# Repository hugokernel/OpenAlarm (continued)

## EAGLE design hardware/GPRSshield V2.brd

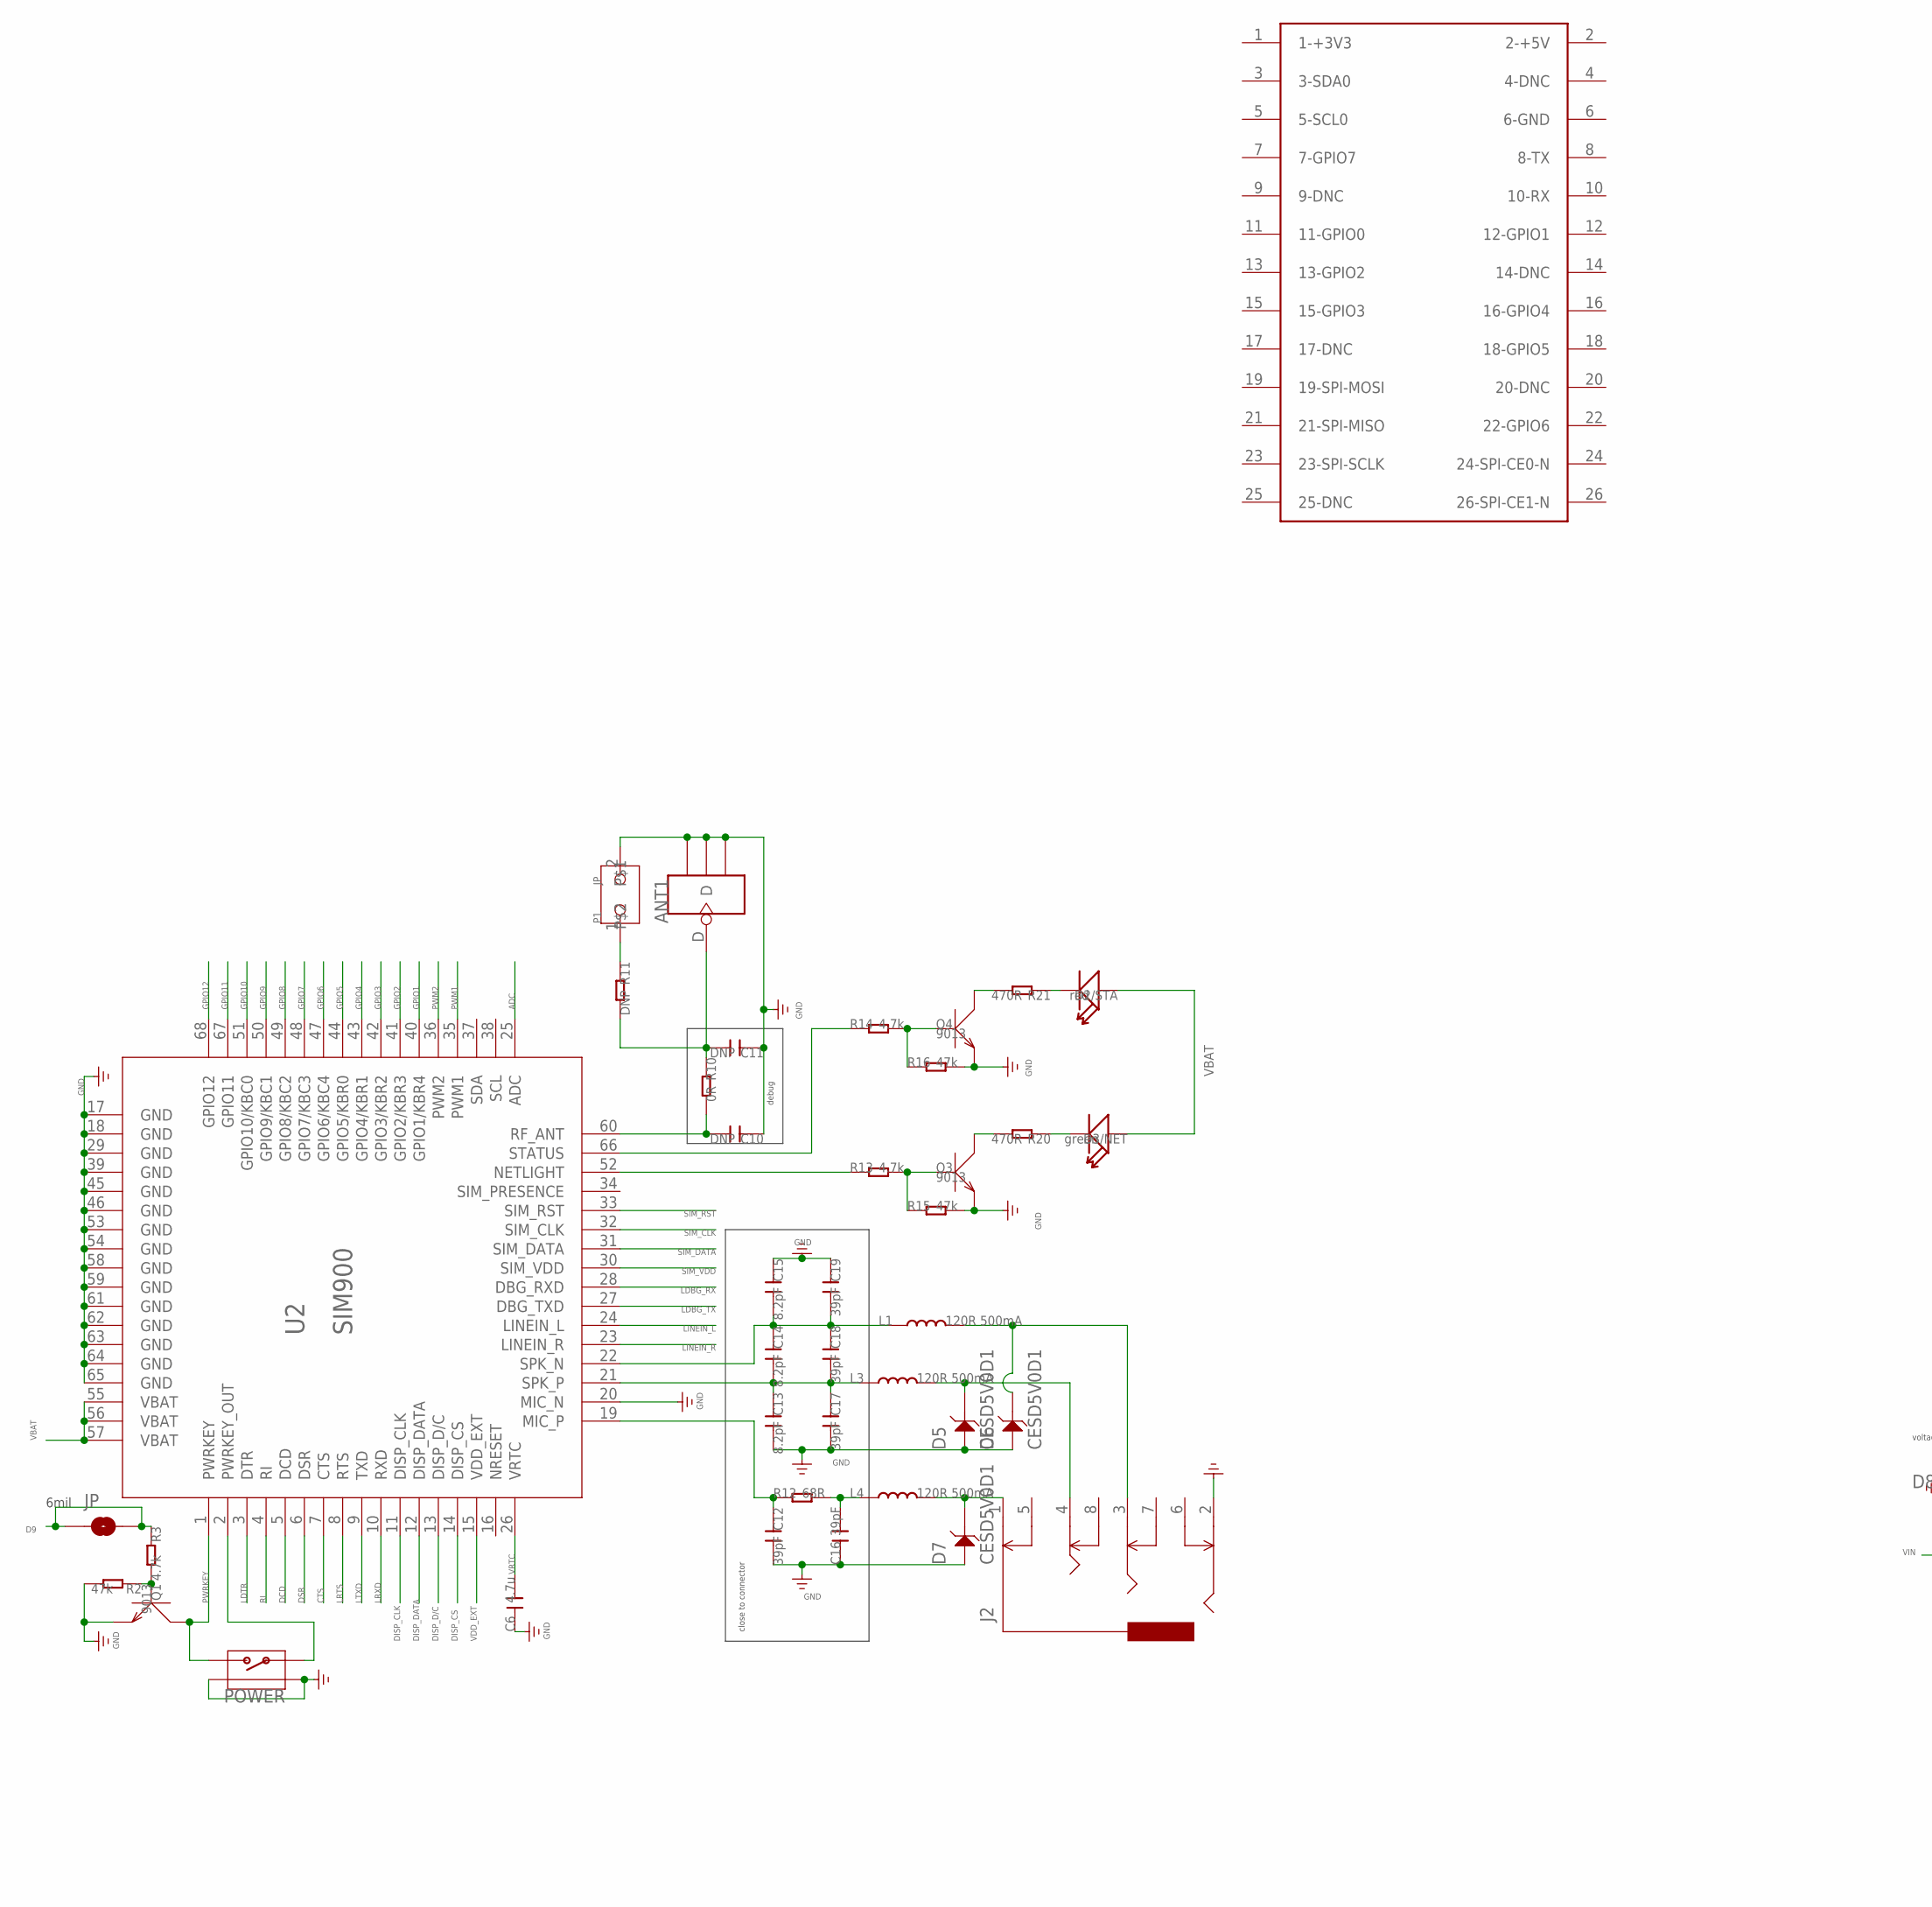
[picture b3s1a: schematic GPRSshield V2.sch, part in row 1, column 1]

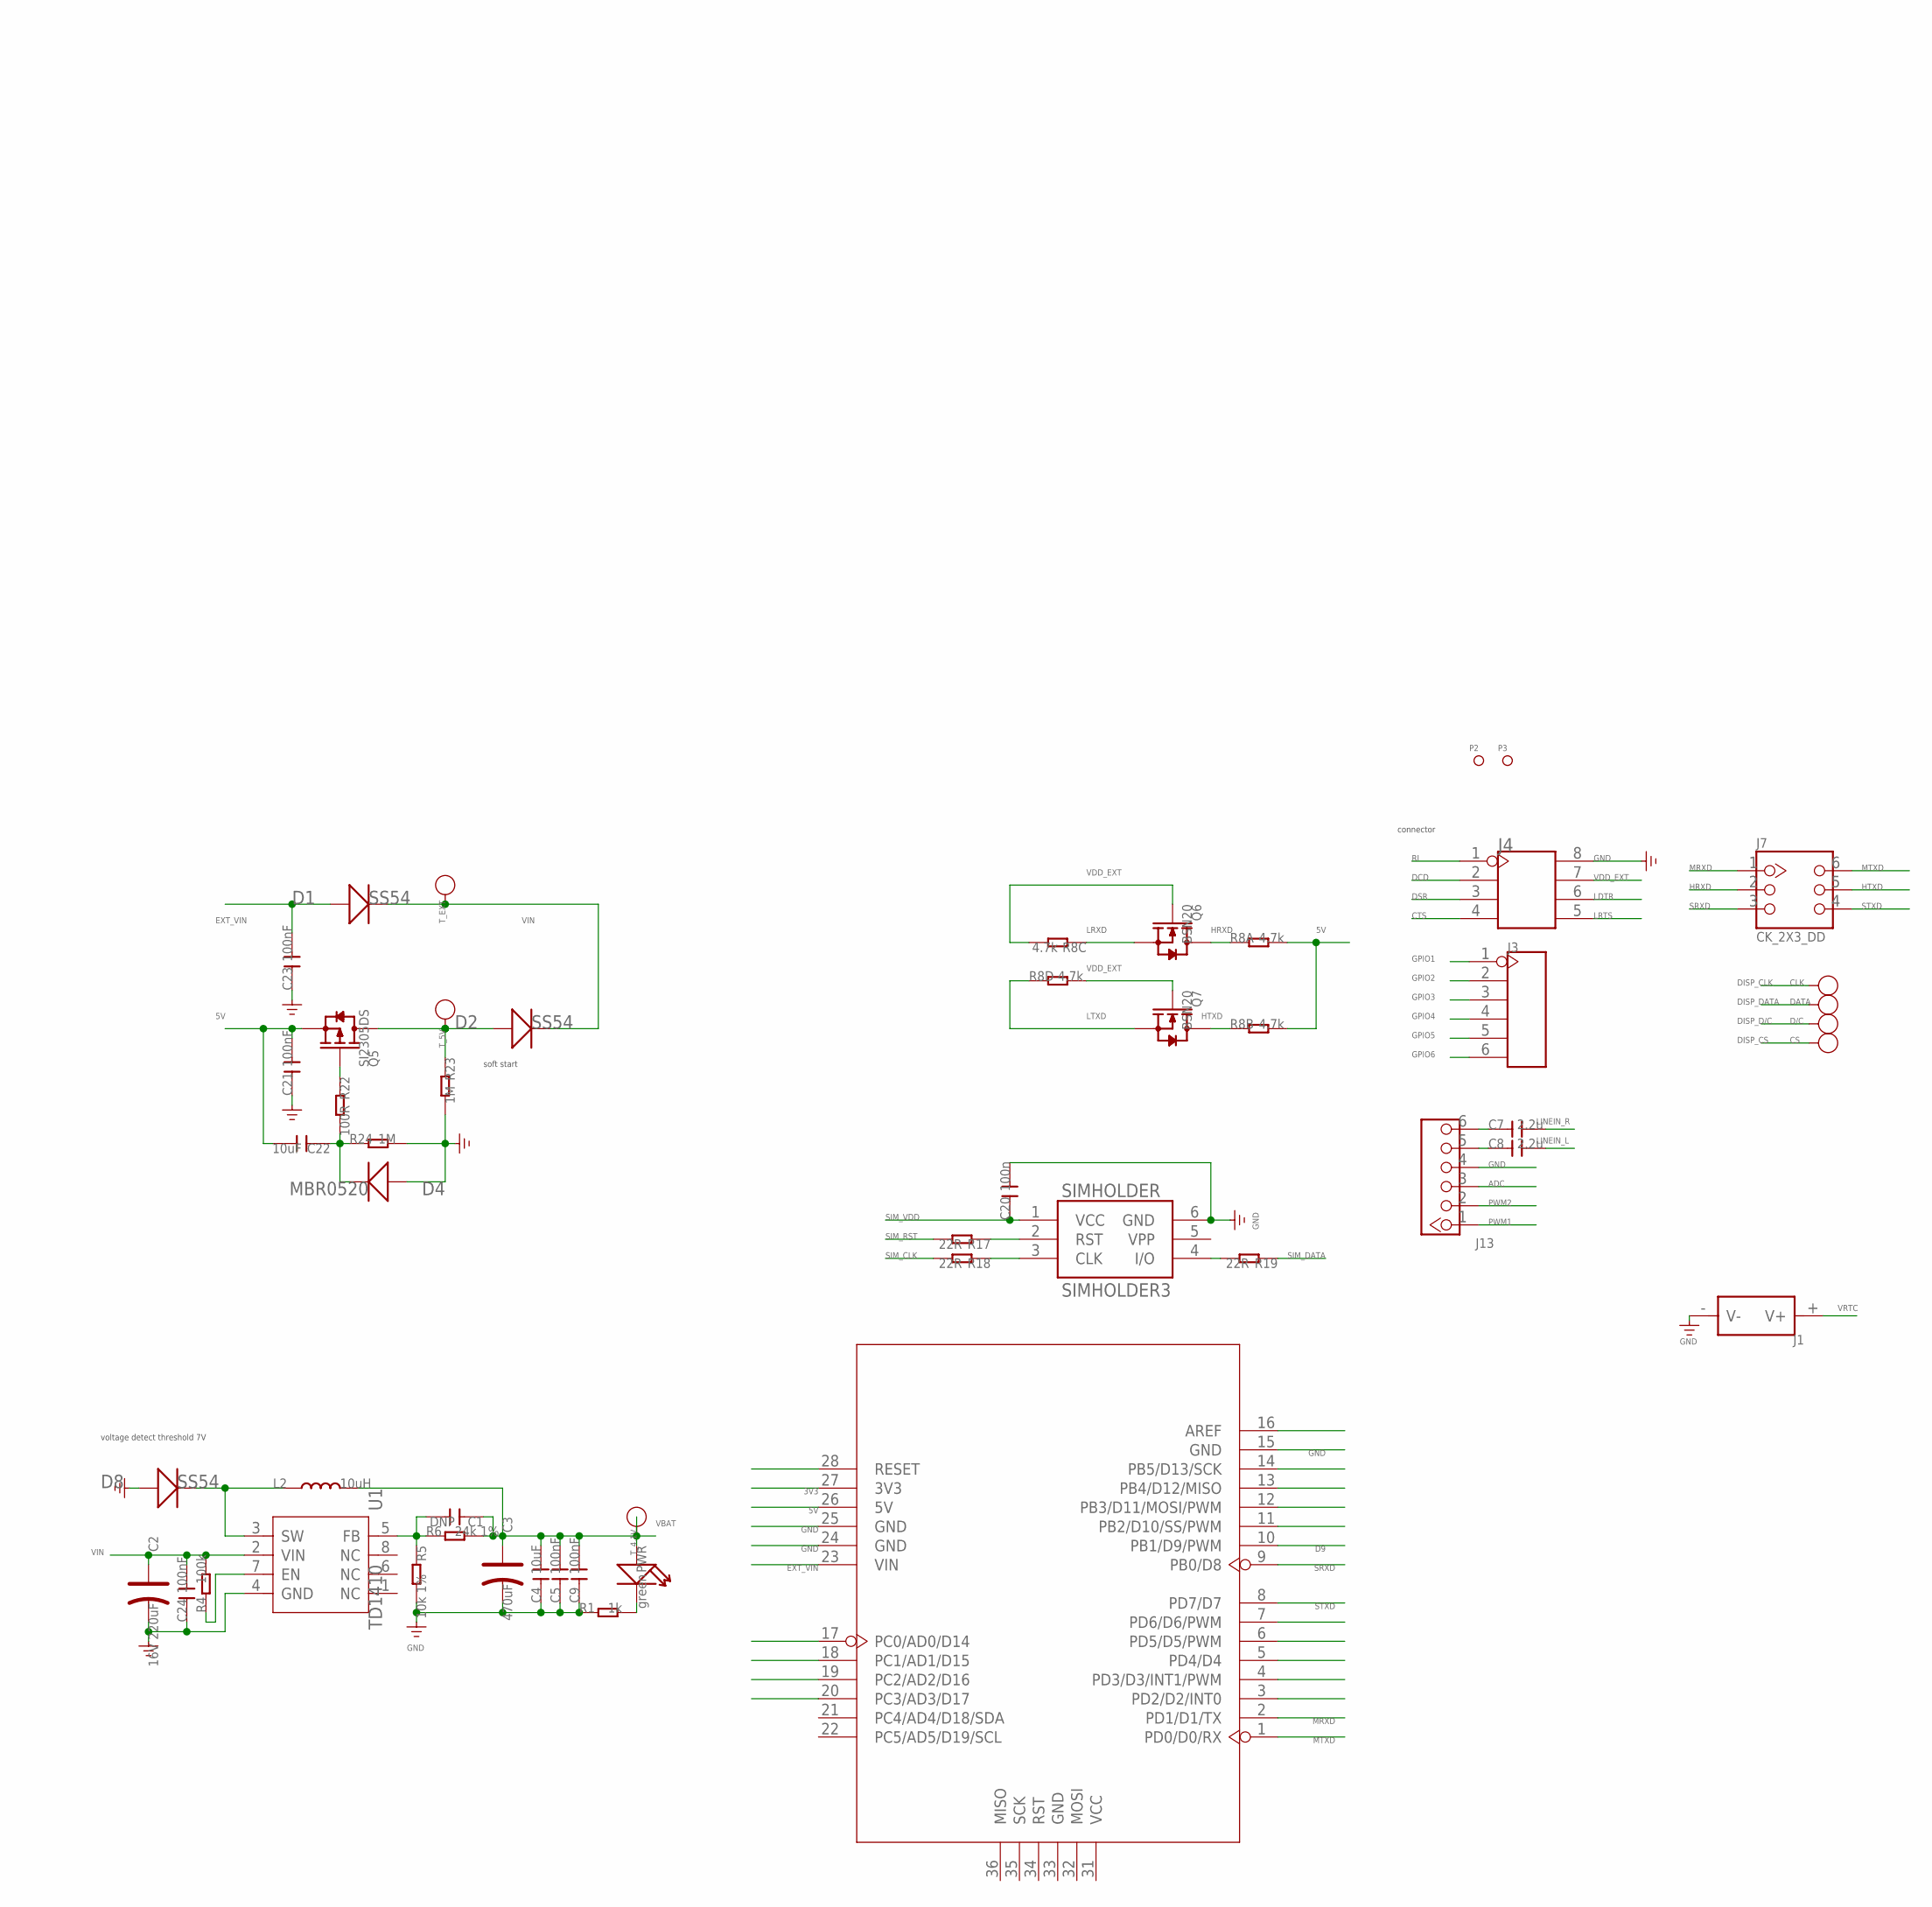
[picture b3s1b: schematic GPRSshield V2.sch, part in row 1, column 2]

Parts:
ANT1: ANTENNA-U-FL; 4P-U-FL
C1, C10, C11: DNP; C0603
C2: 16V 220uF; ELECTRO-SMD-D-5.6MM
C3: 470uF; AVX-D
C4, C22: 10uF; C0805
C5, C9, C21, C23, C24: 100nF; C0603
C6: 4.7u; C0805
C7, C8: 2.2u; C0805
C12, C16, C17, C18, C19: 39pF; C0603
C13, C14, C15: 8.2pF; C0603
C20: 100n; C0603
CLK: PAD-TEST-POINT-CIRCLE'4545'; TP_4545
CS: PAD-TEST-POINT-CIRCLE'4545'; TP_4545
D1, D2, D8: SS54; SMB
D2/STA: red; LED-0603
D3/NET: green; LED-0603
D4: MBR0520; SOD123-2.7X1.6
D5, D6, D7: CESD5V0D1; SOD123-2.7X1.6
D/C: PAD-TEST-POINT-CIRCLE'4545'; TP_4545
DATA: PAD-TEST-POINT-CIRCLE'4545'; TP_4545
J1: HOLDER-BAT; SMD-CR1220-2
J2: AUDIO-8P'PJ-3536-L6S'; 8P-3.5-SMD
J3: HEADER-6P-65/35MIL; 6P-2.54-65/35MIL
J4: HEADER-2X4P-2.54; 2X4P-2.54
J7: CK_2X3_DD; CK_2X3
J13: HEADER_1X6; CK_1X6
JP: PAD-SOLDERJUMPERNC; 2P-SMD-3.3X2
L1, L3, L4: 120R 500mA; L0603
L2: 10uH; L0630
P1: JP
P2, P3: PAD-MARK; ROUND-MARK-1.0
POWER: BUTTON-4P-REINFORCE'TS-118E'; 4P-SMD-7X3.5X3.5H
PWR: green; D0603
Q1, Q3, Q4: 9013; SOT23
Q5: SI2305DS; SOT23
Q6, Q7: BSN20; SOT23
R1: 1k; R0603
R2, R15, R16: 47k; R0603
R3, R13, R14: 4.7k; R0603
R4: 100k; R0603
R5: 10k 1%; R0603
R6: 24k 1%; R0603
R8: 4.7k; 1206-8-3.3X2.4
R10: 0R; R0603
R11: DNP; R0603
R12: 68R; R0603
R17, R18, R19: 22R; R0603
R20, R21: 470R; R0603
R22: 100R; R0603
R23, R24: 1M; R0603
SIMHOLDER: SIMHOLDER3
T_4.1V, T_5V: PAD-TEST-POINT-CIRCLE'4545'; TP_4545; PARTNO DNP
T_EXT: PAD-TEST-POINT-CIRCLE'4545'; TP_4545; PARTNO DNP
U1: TD1410; SOP8
U2: SIM900
U3: ARDUINO'W/O-SILK'; ARDUINO-W/O-SILK
U$4: RASPBERRY-PI

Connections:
3V3: U3.27 (3V3)
5V: C21.2, C22.2, Q5.2 (S), R8.7 (2), R8.8 (2), U3.26 (5V)
ADC: J13.3, U2.25 (ADC)
CTS: J4.4, U2.7 (CTS)
D9: JP.1, JP.2, R3.1, U3.10 (PB1/D9/PWM)
DCD: J4.2, U2.5 (DCD)
DISP_CLK: CLK.T, U2.11 (DISP_CLK)
DISP_CS: CS.T, U2.14 (DISP_CS)
DISP_D/C: D/C.T, U2.13 (DISP_D/C)
DISP_DATA: DATA.T, U2.12 (DISP_DATA)
DSR: J4.3, U2.6 (DSR)
EXT_VIN: C23.2, D1.+, U3.23 (VIN)
GND: ANT1.GND1, ANT1.GND2, ANT1.GND3, C2.-, C3.-, C4.1, C5.1, C6.1, C9.1, C10.1, C11.1, C12.2, C13.2, C15.1, C16.1, C17.2, C19.1, C20.2, C21.1, C23.1, C24.1, D4.1 (+), D5.1, D6.1, D7.1, D8.+, J1.- (V-), J2.2, J4.8, J13.4, P1.2, POWER.S1, POWER.S2, Q1.2 (E), Q3.2 (E), Q4.2 (E), R1.1, R2.2, R5.2, R15.2, R16.2, R23.2, R24.2, SIMHOLDER.6 (GND), U1.4 (GND), U2.17 (GND), U2.18 (GND), U2.20 (MIC_N), U2.29 (GND), U2.39 (GND), U2.45 (GND), U2.46 (GND), U2.53 (GND), U2.54 (GND), U2.58 (GND), U2.59 (GND), U2.61 (GND), U2.62 (GND), U2.63 (GND), U2.64 (GND), U2.65 (GND), U3.15 (GND), U3.24 (GND), U3.25 (GND)
GPIO1: J3.1, U2.40 (GPIO1/KBR4)
GPIO2: J3.2, U2.41 (GPIO2/KBR3)
GPIO3: J3.3, U2.42 (GPIO3/KBR2)
GPIO4: J3.4, U2.43 (GPIO4/KBR1)
GPIO5: J3.5, U2.44 (GPIO5/KBR0)
GPIO6: J3.6, U2.47 (GPIO6/KBC4)
GPIO7: U2.48 (GPIO7/KBC3)
GPIO8: U2.49 (GPIO8/KBC2)
GPIO9: U2.50 (GPIO9/KBC1)
GPIO10: U2.51 (GPIO10/KBC0)
GPIO11: U2.67 (GPIO11)
GPIO12: U2.68 (GPIO12)
HRXD: J7.2, Q6.3 (D), R8.1
HTXD: J7.5, Q7.3 (D), R8.2 (1)
LDBG_RX: U2.28 (DBG_RXD)
LDBG_TX: U2.27 (DBG_TXD)
LDTR: J4.6, U2.3 (DTR)
LINEIN_L: C8.2, U2.24 (LINEIN_L)
LINEIN_R: C7.2, U2.23 (LINEIN_R)
LRTS: J4.5, U2.8 (RTS)
LRXD: Q6.2 (S), R8.3 (1), U2.10 (RXD)
LTXD: Q7.2 (S), R8.4 (1), U2.9 (TXD)
MRXD: J7.1, U3.2 (PD1/D1/TX)
MTXD: J7.6, U3.1 (PD0/D0/RX)
unnamed: C10.2, R10.2, U2.60 (RF_ANT)
unnamed: D2.+, Q5.3 (D), R23.1, T_5V.T
unnamed: Q3.3 (C), R20.2
unnamed: R19.2, SIMHOLDER.4 (I/O)
unnamed: R18.1, SIMHOLDER.3 (CLK)
unnamed: R17.1, SIMHOLDER.2 (RST)
unnamed: D3/NET.-, R20.1
unnamed: Q3.1 (B), R13.2, R15.1
unnamed: PWR.-, R1.2
unnamed: R13.1, U2.52 (NETLIGHT)
unnamed: POWER.1, U2.2 (PWRKEY_OUT)
unnamed: R4.1, U1.7 (EN)
unnamed: C12.1, R12.1, U2.19 (MIC_P)
unnamed: C13.1, C14.2, C17.1, C18.2, L3.1, U2.21 (SPK_P)
unnamed: Q4.3 (C), R21.2
unnamed: D2/STA.-, R21.1
unnamed: Q4.1 (B), R14.2, R16.1
unnamed: C14.1, C15.2, C18.1, C19.2, L1.1, U2.22 (SPK_N)
unnamed: R14.1, U2.66 (STATUS)
unnamed: ANT1.D, C11.2, R10.1, R11.2
unnamed: C7.1, J13.6
unnamed: C8.1, J13.5
unnamed: C16.2, L4.1, R12.2
unnamed: Q5.1 (G), R22.1
unnamed: Q1.1 (B), R2.1, R3.2
unnamed: D8.-, L2.1, U1.3 (SW)
unnamed: C22.1, D4.2 (-), R22.2, R24.1
unnamed: D7.2, J2.1, L4.2
unnamed: C1.2, R5.1, R6.1, U1.5 (FB)
unnamed: D5.2, J2.4, L3.2
unnamed: D6.2, J2.3, L1.2
unnamed: P1.1, R11.1
PWM1: J13.1, U2.35 (PWM1)
PWM2: J13.2, U2.36 (PWM2)
PWRKEY: POWER.2, Q1.3 (C), U2.1 (PWRKEY)
RI: J4.1, U2.4 (RI)
SIM_CLK: R18.2, U2.32 (SIM_CLK)
SIM_DATA: R19.1, U2.31 (SIM_DATA)
SIM_RST: R17.2, U2.33 (SIM_RST)
SIM_VDD: C20.1, SIMHOLDER.1 (VCC), U2.30 (SIM_VDD)
SRXD: J7.3, U3.9 (PB0/D8)
STXD: J7.4, U3.8 (PD7/D7)
VBAT: C1.1, C3.+, C4.2, C5.2, C9.2, D2/STA.+, D3/NET.+, L2.2, PWR.+, R6.2, T_4.1V.T, U2.55 (VBAT), U2.56 (VBAT), U2.57 (VBAT)
VDD_EXT: J4.7, Q6.1 (G), Q7.1 (G), R8.5 (2), R8.6 (2), U2.15 (VDD_EXT)
VIN: C2.+, C24.2, D1.-, D2.-, R4.2, T_EXT.T, U1.2 (VIN)
VRTC: C6.2, J1.+ (V+), U2.26 (VRTC)

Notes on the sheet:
close to connector
debug
soft start
voltage detect threshold 7V
connector
6mil

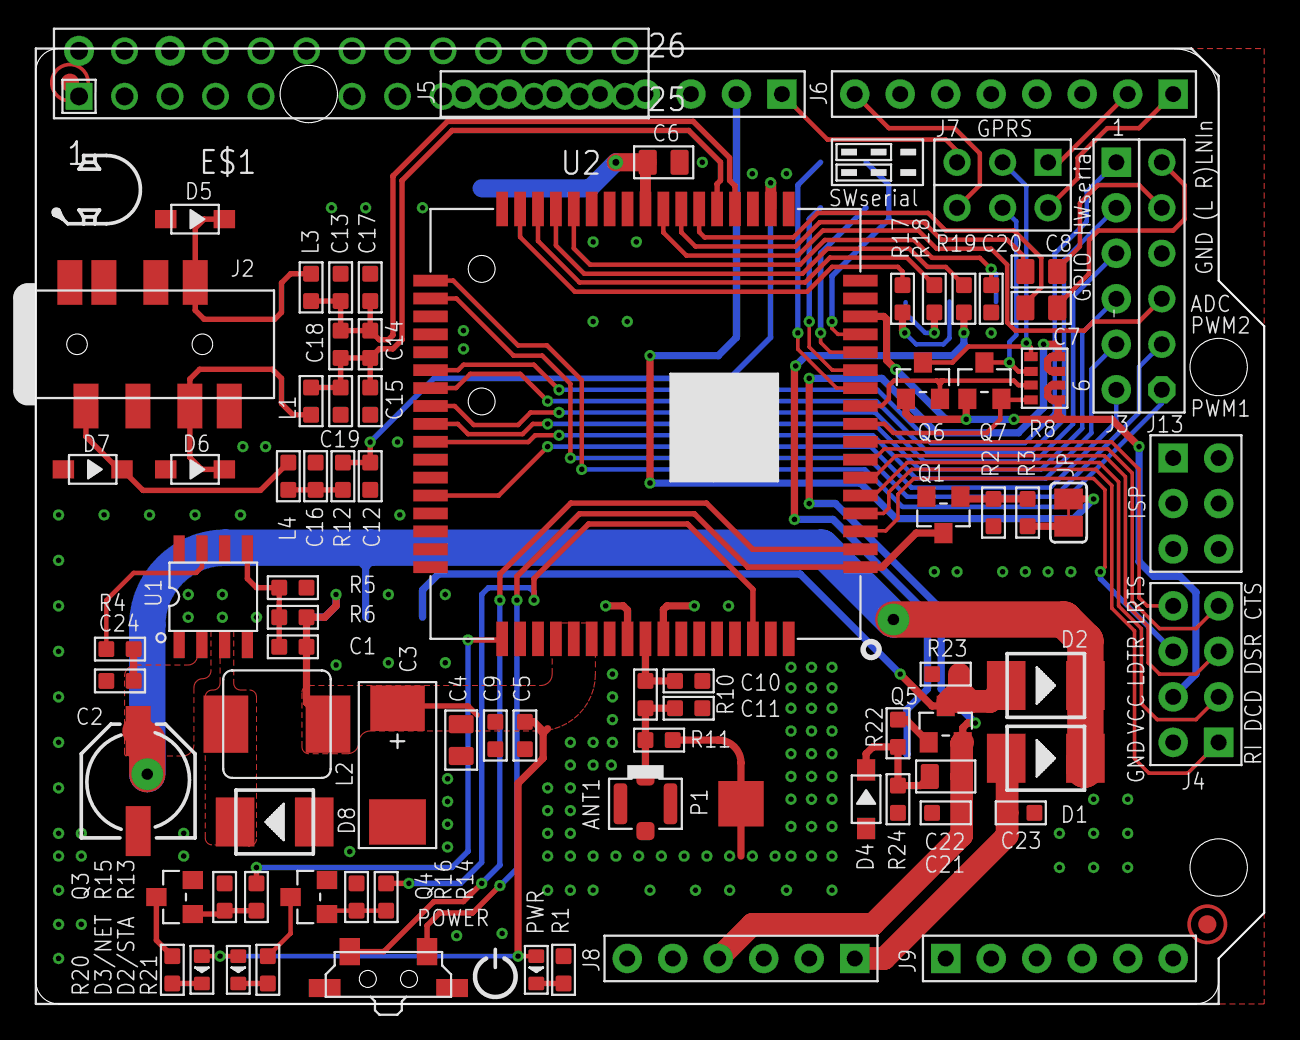
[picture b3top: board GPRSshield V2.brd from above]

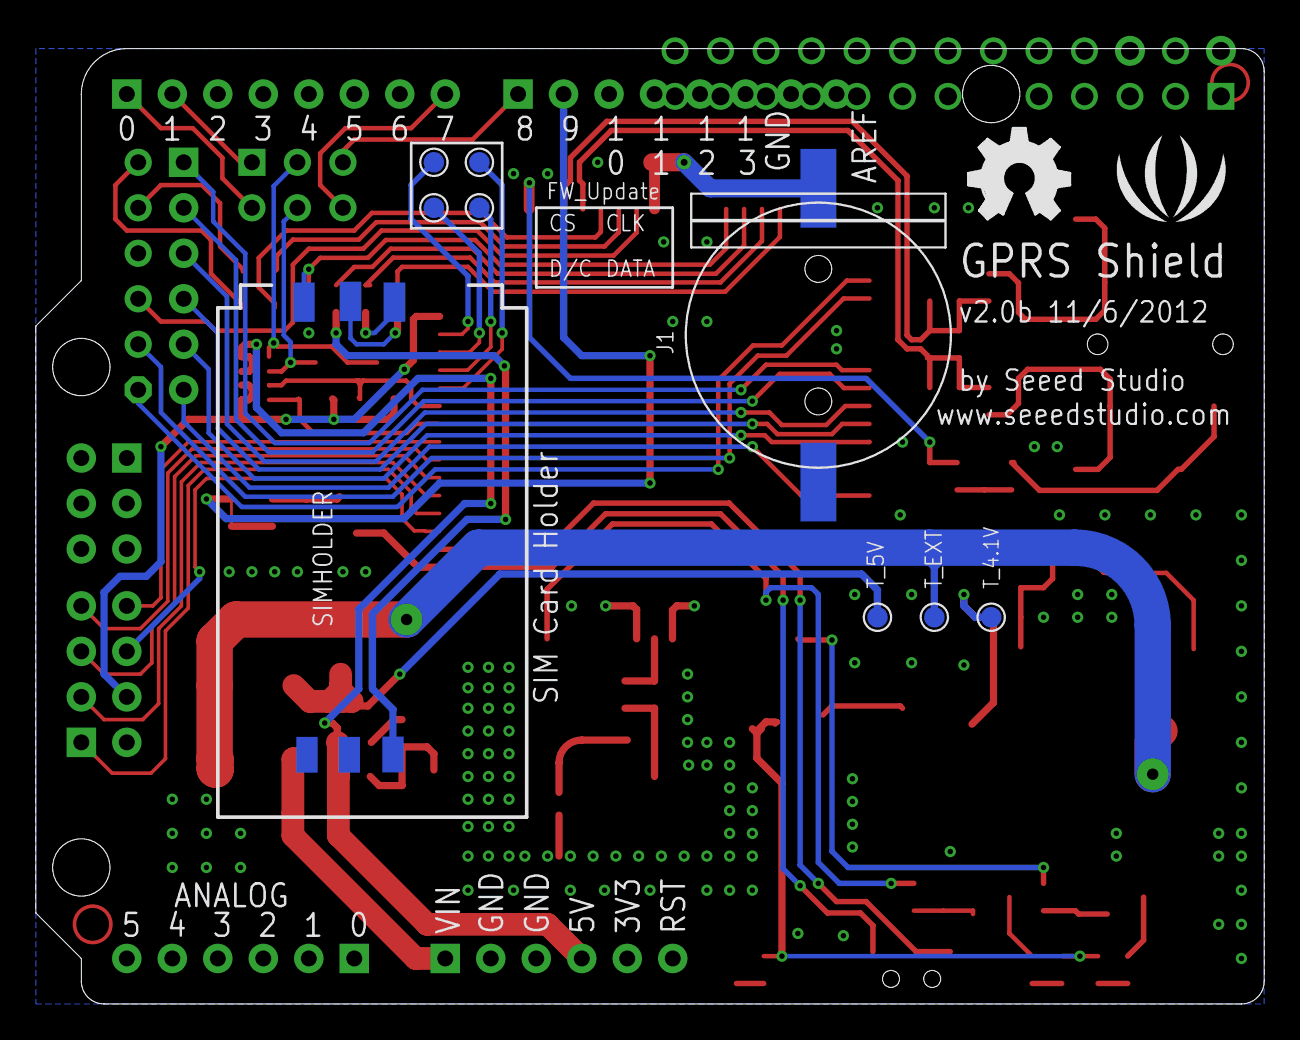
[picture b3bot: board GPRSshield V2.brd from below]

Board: 2 copper layers, 68.6 x 53.3 mm, 92 parts (11 on the bottom side), 74 nets.

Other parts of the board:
E$1: RASPBERRY-PI
U$26: LOGO_SILK
U$28: OSHW_FILLX200_NOTEXT

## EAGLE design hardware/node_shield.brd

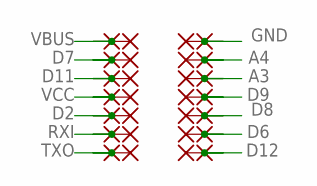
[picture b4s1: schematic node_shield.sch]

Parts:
PAD1, PAD2, PAD3, PAD4, PAD5, PAD6, PAD7, PAD8, PAD9, PAD10, PAD11, PAD12, PAD13, PAD14, PAD15, PAD16, PAD17, PAD18, PAD19, PAD20, PAD21, PAD22, PAD23, PAD24, PAD25, PAD26, PAD27, PAD28: SMD2; SMD1,27-2,54

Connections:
A3: PAD6.1, PAD24.1
A4: PAD5.1, PAD23.1
D2: PAD12.1, PAD19.1
D6: PAD4.1, PAD27.1
D7: PAD2.1, PAD16.1
D8: PAD11.1, PAD26.1
D9: PAD1.1, PAD25.1
D11: PAD7.1, PAD17.1
D12: PAD3.1, PAD28.1
GND: PAD8.1, PAD22.1
RXI: PAD14.1, PAD20.1
TXO: PAD13.1, PAD21.1
VBUS: PAD9.1, PAD15.1
VCC: PAD10.1, PAD18.1

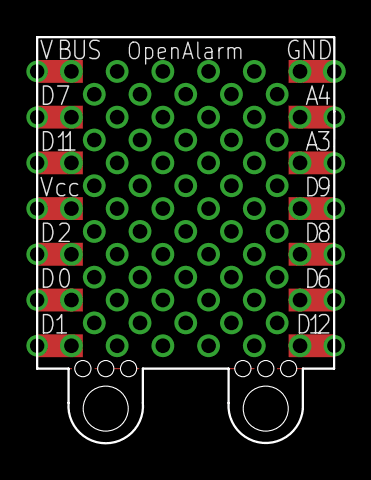
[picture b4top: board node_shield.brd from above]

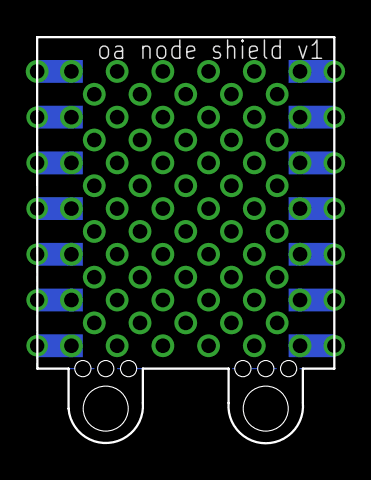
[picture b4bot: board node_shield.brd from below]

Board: 2 copper layers, 16.5 x 22.6 mm, 28 parts (14 on the bottom side), 14 nets.

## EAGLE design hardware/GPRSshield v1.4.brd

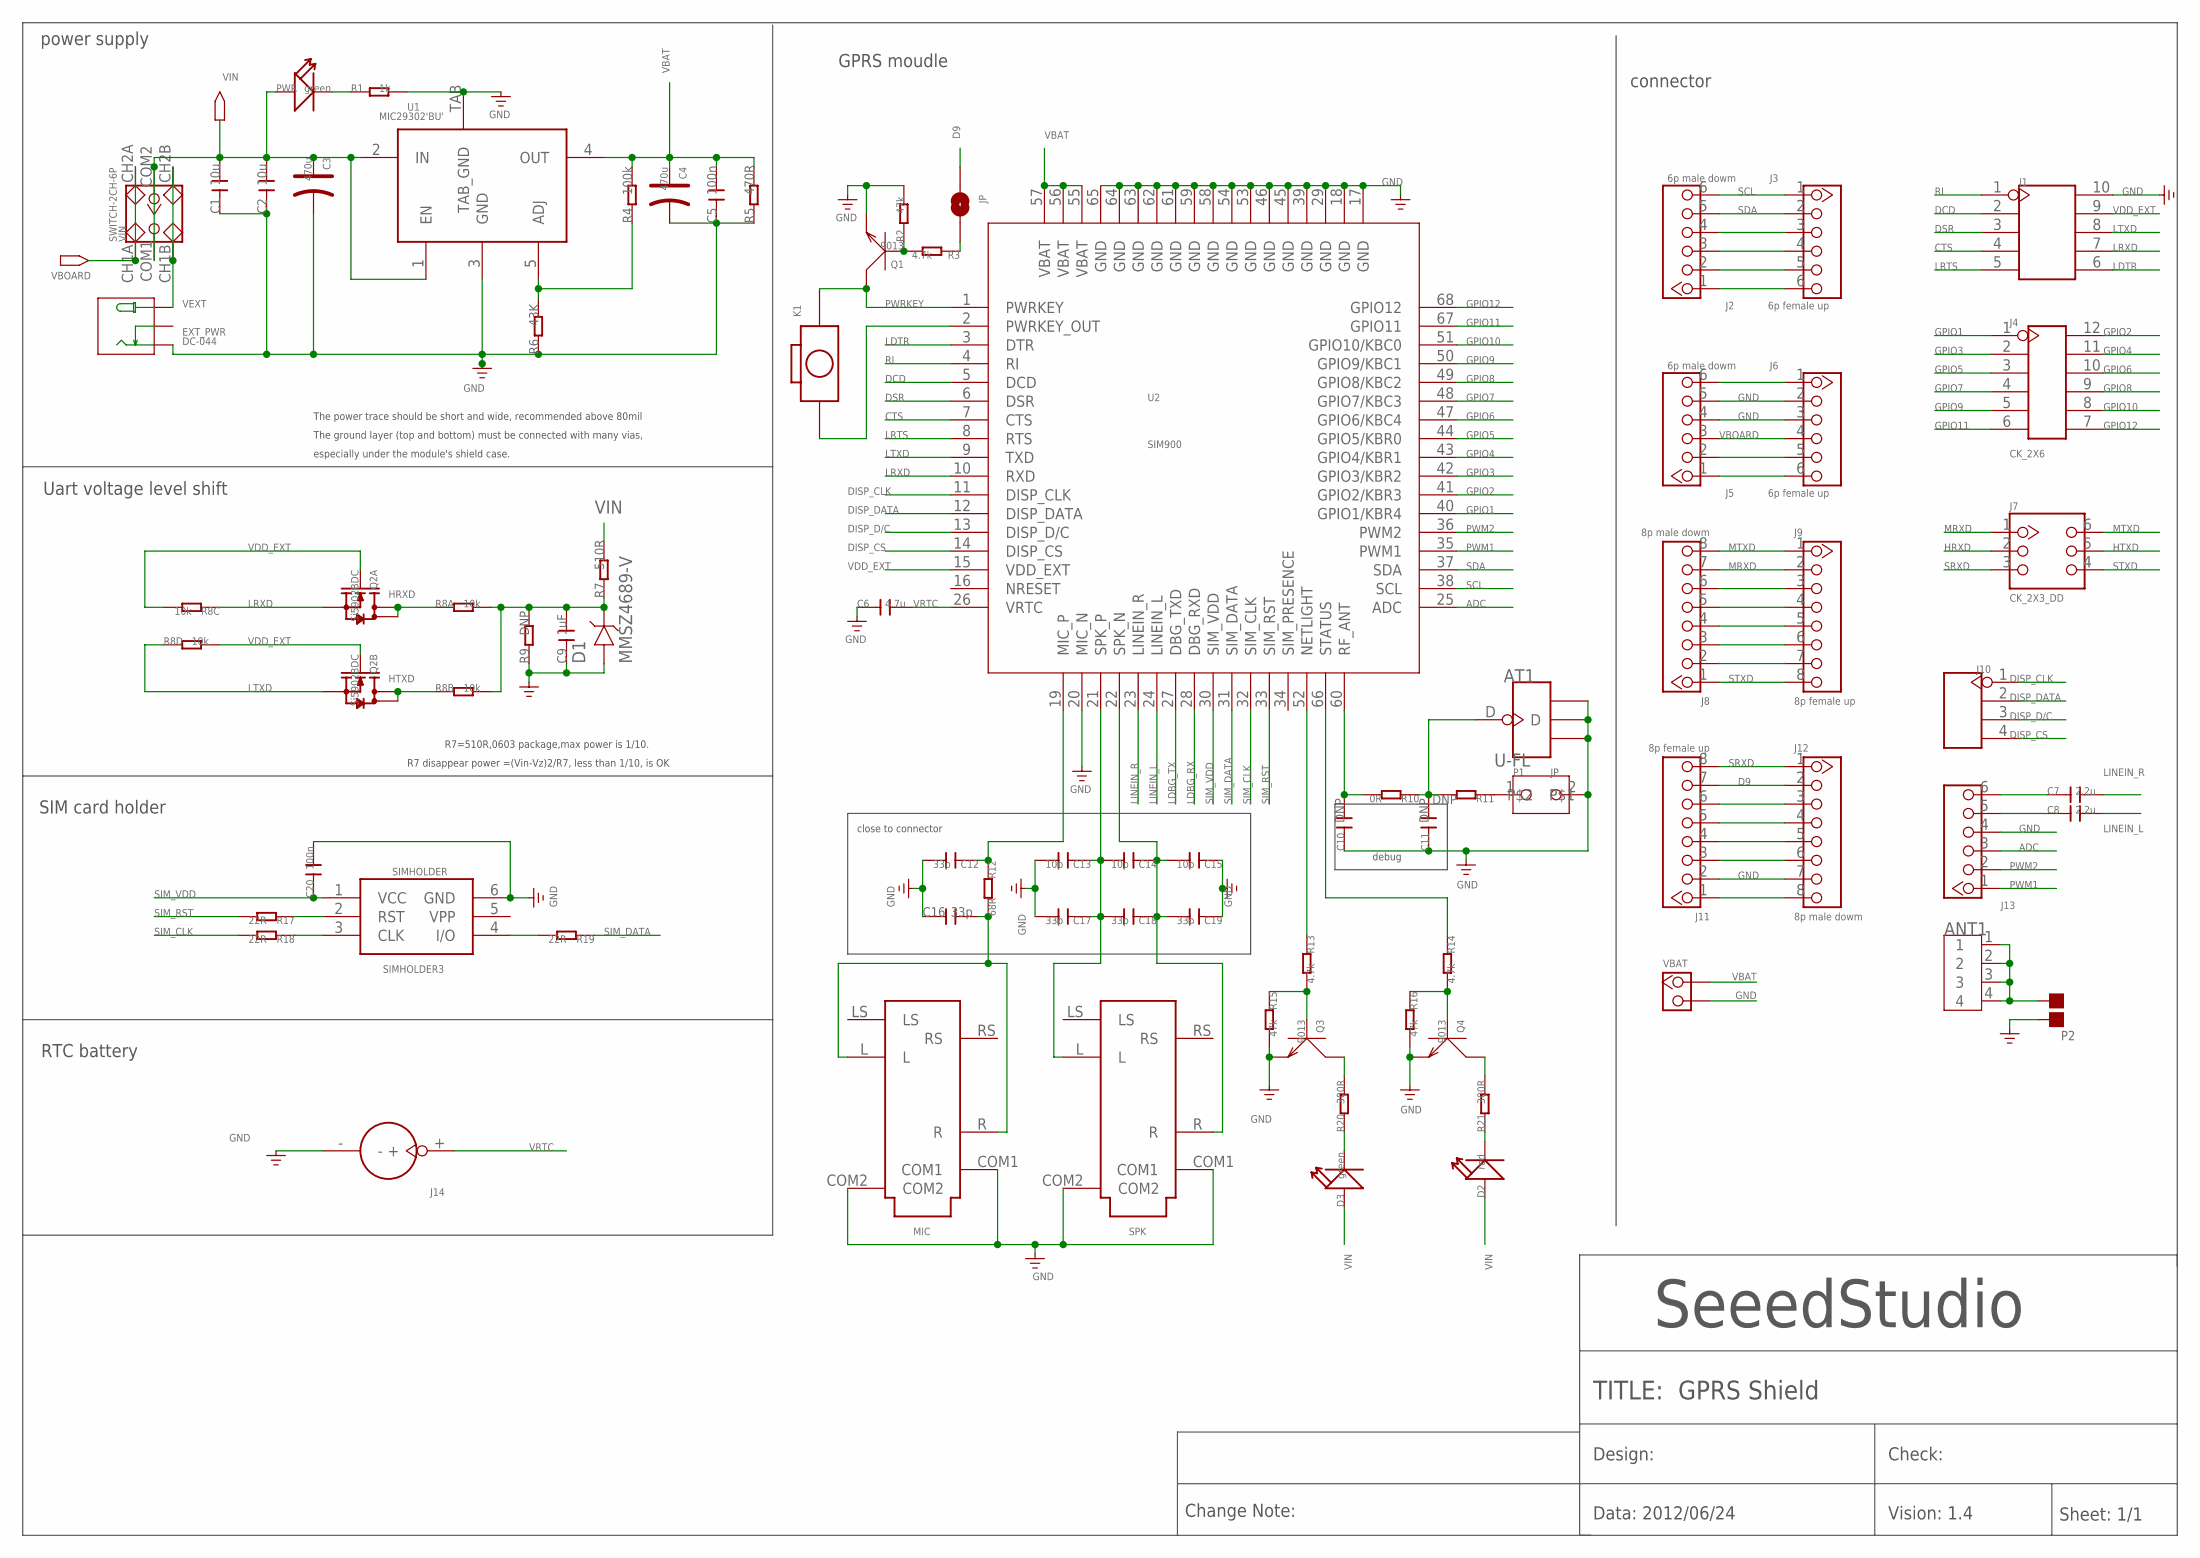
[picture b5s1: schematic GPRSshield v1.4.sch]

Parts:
ANT1: ANTENNA-SMA-IPX; SMA-TO-IPX
AT1: U-FL; 4P-U-FL
C1, C2: 10u; 0603
C3, C4: 470u; AVX_D
C5, C20: 100n; 0603
C6: 4.7u; 0805
C7, C8: 2.2u; 0603
C9: 1uF; 0603
C10, C11: DNP; 0402
C12, C16: 33p; 0603
C13, C14, C15: 10p; 0402
C17, C18, C19: 33p; 0402
D1: MMSZ4689-V; SOD123-2.7X1.6
D2: red; LED-0603
D3: green; LED-0603
EXT_PWR: DC-044; DC-404
J1: HEADER-2X5P-2.54; 2X5P-2.54
J2, J5: 6p male dowm; CK_1X6
J3, J6: 6p female up; CK_1X6
J4: CK_2X6
J7: CK_2X3_DD; CK_2X3
J8, J12: 8p male dowm; CK_1X8
J9, J11: 8p female up; CK_1X8
J10: HEADER-4P'2.54-90D-FEMALE'; 4P-2.54-90D-FEMALE
J13: HEADER_1X6; CK_1X6
J14: HOLDER-BATTERY-2P-CR1220; CR1220
JP: PAD-SOLDERJUMPERNC; 2P-SMD-3.3X2
K1: BOTTON_1_DP; BTN_5.0_RST
MIC: AUDIO-SMT; 3.5-SMD
P1: JP
P2: PAD-JUMPER-2P; 2P-SMD-1.78X1.27
PWR: green; D0603
Q1, Q3, Q4: 9013; SOT23
Q2: Si5902BDC; 1206-8
R1: 1k; 0603
R2, R15, R16: 47k; 0603
R3, R13, R14: 4.7k; 0603
R4: 100k; 0603
R5: 470R; 0603
R6: 43K; 0603
R7: 510R; 0603
R8: 10k; 1206-8-3.3X2.4
R9: DNP; 0603
R10: 0R; 0402
R11: DNP; 0402
R12: 68R; 0603
R17, R18, R19: 22R; 0603
R20, R21: 300R; 0603
SIMHOLDER: SIMHOLDER3
SPK: AUDIO-SMT; 3.5-SMD
U1: MIC29302'BU'; TO-263
U2: SIM900
VBAT: DNP; CK_1*2
VIN: SWITCH-2CH-6P; 6P-2CH-2.54-7.6X3.0

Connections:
ADC: J13.3, U2.25 (ADC)
CTS: J1.4, U2.7 (CTS)
D9: J11.7, J12.2, JP.1
DCD: J1.2, U2.5 (DCD)
DISP_CLK: J10.1, U2.11 (DISP_CLK)
DISP_CS: J10.4, U2.14 (DISP_CS)
DISP_D/C: J10.3, U2.13 (DISP_D/C)
DISP_DATA: J10.2, U2.12 (DISP_DATA)
DSR: J1.3, U2.6 (DSR)
GND: AT1.GND1, AT1.GND2, AT1.GND3, C1.1, C2.1, C3.-, C4.-, C5.1, C6.1, C9.1, C10.1, C11.1, C12.2, C13.2, C15.1, C16.1, C17.2, C19.1, C20.2, D1.1, EXT_PWR.-, J1.10, J5.4, J5.5, J6.2, J6.3, J11.2, J12.7, J13.4, J14.-, MIC.COM1, MIC.COM2, P1.2, P2.2, Q1.2 (E), Q3.2 (E), Q4.2 (E), R1.2, R2.2, R5.1, R6.1, R9.1, R15.2, R16.2, SIMHOLDER.6 (GND), SPK.COM1, SPK.COM2, U1.3 (GND), U1.TAB (TAB_GND), U2.17 (GND), U2.18 (GND), U2.20 (MIC_N), U2.29 (GND), U2.39 (GND), U2.45 (GND), U2.46 (GND), U2.53 (GND), U2.54 (GND), U2.58 (GND), U2.59 (GND), U2.61 (GND), U2.62 (GND), U2.63 (GND), U2.64 (GND), U2.65 (GND), VBAT.2
GPIO1: J4.1, U2.40 (GPIO1/KBR4)
GPIO2: J4.12, U2.41 (GPIO2/KBR3)
GPIO3: J4.2, U2.42 (GPIO3/KBR2)
GPIO4: J4.11, U2.43 (GPIO4/KBR1)
GPIO5: J4.3, U2.44 (GPIO5/KBR0)
GPIO6: J4.10, U2.47 (GPIO6/KBC4)
GPIO7: J4.4, U2.48 (GPIO7/KBC3)
GPIO8: J4.9, U2.49 (GPIO8/KBC2)
GPIO9: J4.5, U2.50 (GPIO9/KBC1)
GPIO10: J4.8, U2.51 (GPIO10/KBC0)
GPIO11: J4.6, U2.67 (GPIO11)
GPIO12: J4.7, U2.68 (GPIO12)
HRXD: J7.2, Q2.7 (D), Q2.8 (D), R8.1
HTXD: J7.5, Q2.5 (D), Q2.6 (D), R8.2 (1)
LDBG_RX: U2.28 (DBG_RXD)
LDBG_TX: U2.27 (DBG_TXD)
LDTR: J1.6, U2.3 (DTR)
LINEIN_L: C8.2, U2.24 (LINEIN_L)
LINEIN_R: C7.2, U2.23 (LINEIN_R)
LRTS: J1.5, U2.8 (RTS)
LRXD: J1.7, Q2.1 (S), R8.3 (1), U2.10 (RXD)
LTXD: J1.8, Q2.3 (S), R8.4 (1), U2.9 (TXD)
MRXD: J7.1, J8.7, J9.2
MTXD: J7.6, J8.8, J9.1
unnamed: C10.2, R10.2, U2.60 (RF_ANT)
unnamed: R4.1, R6.2, U1.5 (ADJ)
unnamed: Q3.3 (C), R20.2
unnamed: R19.2, SIMHOLDER.4 (I/O)
unnamed: R18.1, SIMHOLDER.3 (CLK)
unnamed: R17.1, SIMHOLDER.2 (RST)
unnamed: D3.-, R20.1
unnamed: Q3.1 (B), R13.2, R15.1
unnamed: C9.2, D1.2, R7.1, R8.7 (2), R8.8 (2), R9.2
unnamed: R13.1, U2.52 (NETLIGHT)
unnamed: K1.P$1 (1), U2.2 (PWRKEY_OUT)
unnamed: ANT1.1, ANT1.2, ANT1.3, ANT1.4, P2.1
unnamed: C12.1, R12.1, U2.19 (MIC_P)
unnamed: JP.2, R3.1
unnamed: C13.1, C14.2, C17.1, C18.2, SPK.L, U2.21 (SPK_P)
unnamed: Q4.3 (C), R21.2
unnamed: D2.-, R21.1
unnamed: Q4.1 (B), R14.2, R16.1
unnamed: C14.1, C15.2, C18.1, C19.2, SPK.R, U2.22 (SPK_N)
unnamed: R14.1, U2.66 (STATUS)
unnamed: AT1.D, C11.2, R10.1, R11.2
unnamed: P1.1, R11.1
unnamed: C7.1, J13.6
unnamed: J8.6, J9.3
unnamed: J8.5, J9.4
unnamed: J8.4, J9.5
unnamed: J8.3, J9.6
unnamed: J8.2, J9.7
unnamed: C8.1, J13.5
unnamed: C16.2, MIC.L, MIC.R, R12.2
unnamed: J11.6, J12.3
unnamed: J11.5, J12.4
unnamed: J11.4, J12.5
unnamed: J11.3, J12.6
unnamed: Q1.1 (B), R2.1, R3.2
unnamed: J11.1, J12.8
unnamed: J2.4, J3.3
unnamed: J2.3, J3.4
unnamed: J2.2, J3.5
unnamed: J2.1, J3.6
unnamed: J5.6, J6.1
unnamed: J5.2, J6.5
unnamed: J5.1, J6.6
unnamed: PWR.-, R1.1
PWM1: J13.1, U2.35 (PWM1)
PWM2: J13.2, U2.36 (PWM2)
PWRKEY: K1.P$2 (2), Q1.3 (C), U2.1 (PWRKEY)
RI: J1.1, U2.4 (RI)
SCL: J2.6, J3.1, U2.38 (SCL)
SDA: J2.5, J3.2, U2.37 (SDA)
SIM_CLK: R18.2, U2.32 (SIM_CLK)
SIM_DATA: R19.1, U2.31 (SIM_DATA)
SIM_RST: R17.2, U2.33 (SIM_RST)
SIM_VDD: C20.1, SIMHOLDER.1 (VCC), U2.30 (SIM_VDD)
SRXD: J7.3, J11.8, J12.1
STXD: J7.4, J8.1, J9.8
VBAT: C4.+, C5.2, R4.2, R5.2, U1.4 (OUT), U2.55 (VBAT), U2.56 (VBAT), U2.57 (VBAT), VBAT.1
VBOARD: J5.3, J6.4, VIN.CH1A, VIN.CH2A
VDD_EXT: J1.9, Q2.2 (G), Q2.4 (G), R8.5 (2), R8.6 (2), U2.15 (VDD_EXT)
VEXT: EXT_PWR.+, VIN.CH1B, VIN.CH2B
VIN: C1.2, C2.2, C3.+, D2.+, D3.+, PWR.+, R7.2, U1.1 (EN), U1.2 (IN), VIN.COM1, VIN.COM2
VRTC: C6.2, J14.+, U2.26 (VRTC)

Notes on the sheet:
close to connector
debug
TITLE: GPRS Shield
SeeedStudio
Design:
Check:
Data: 2012/06/24
Vision: 1.4
Sheet: 1/1
power supply
The power trace should be short and wide, recommended above 80mil
The ground layer (top and bottom) must be connected with many vias,
especially under the module's shield case.
Uart voltage level shift
R7=510R,0603 package,max power is 1/10.
R7 disappear power =(Vin-Vz)2/R7, less than 1/10, is OK
RTC battery
SIM card holder
GPRS moudle
connector
Change Note:
